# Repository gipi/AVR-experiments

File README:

This repository will contain projects AVR related.

Each project is contained in a directory of its own and in order to
compile it you can

 $ cd <project name>
 $ make upload

It's possible to install the dependencies using the
following command in a Debian-like sistem

 # apt-get install gcc-avr binutils-avr avr-libc

In the libraries/ directory are contained some routines very useful
to AVR projects. Are intended to be incluede in your source code
and not linked since it's very likely that the F_CPU or MCU values are
different from what you expect at compile time.

It's also possible to flash into Arduino this code (not all code will work)
using the ``PROGRAMMER`` variable:

    $ make PROGRAMMER=arduino

if not indicated will use the ``buspirate``. Obvioulsy the code must set the ``MCU``
and ``F_CPU`` accordingly.

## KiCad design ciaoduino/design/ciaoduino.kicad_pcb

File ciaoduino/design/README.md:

Design files created with kicad.

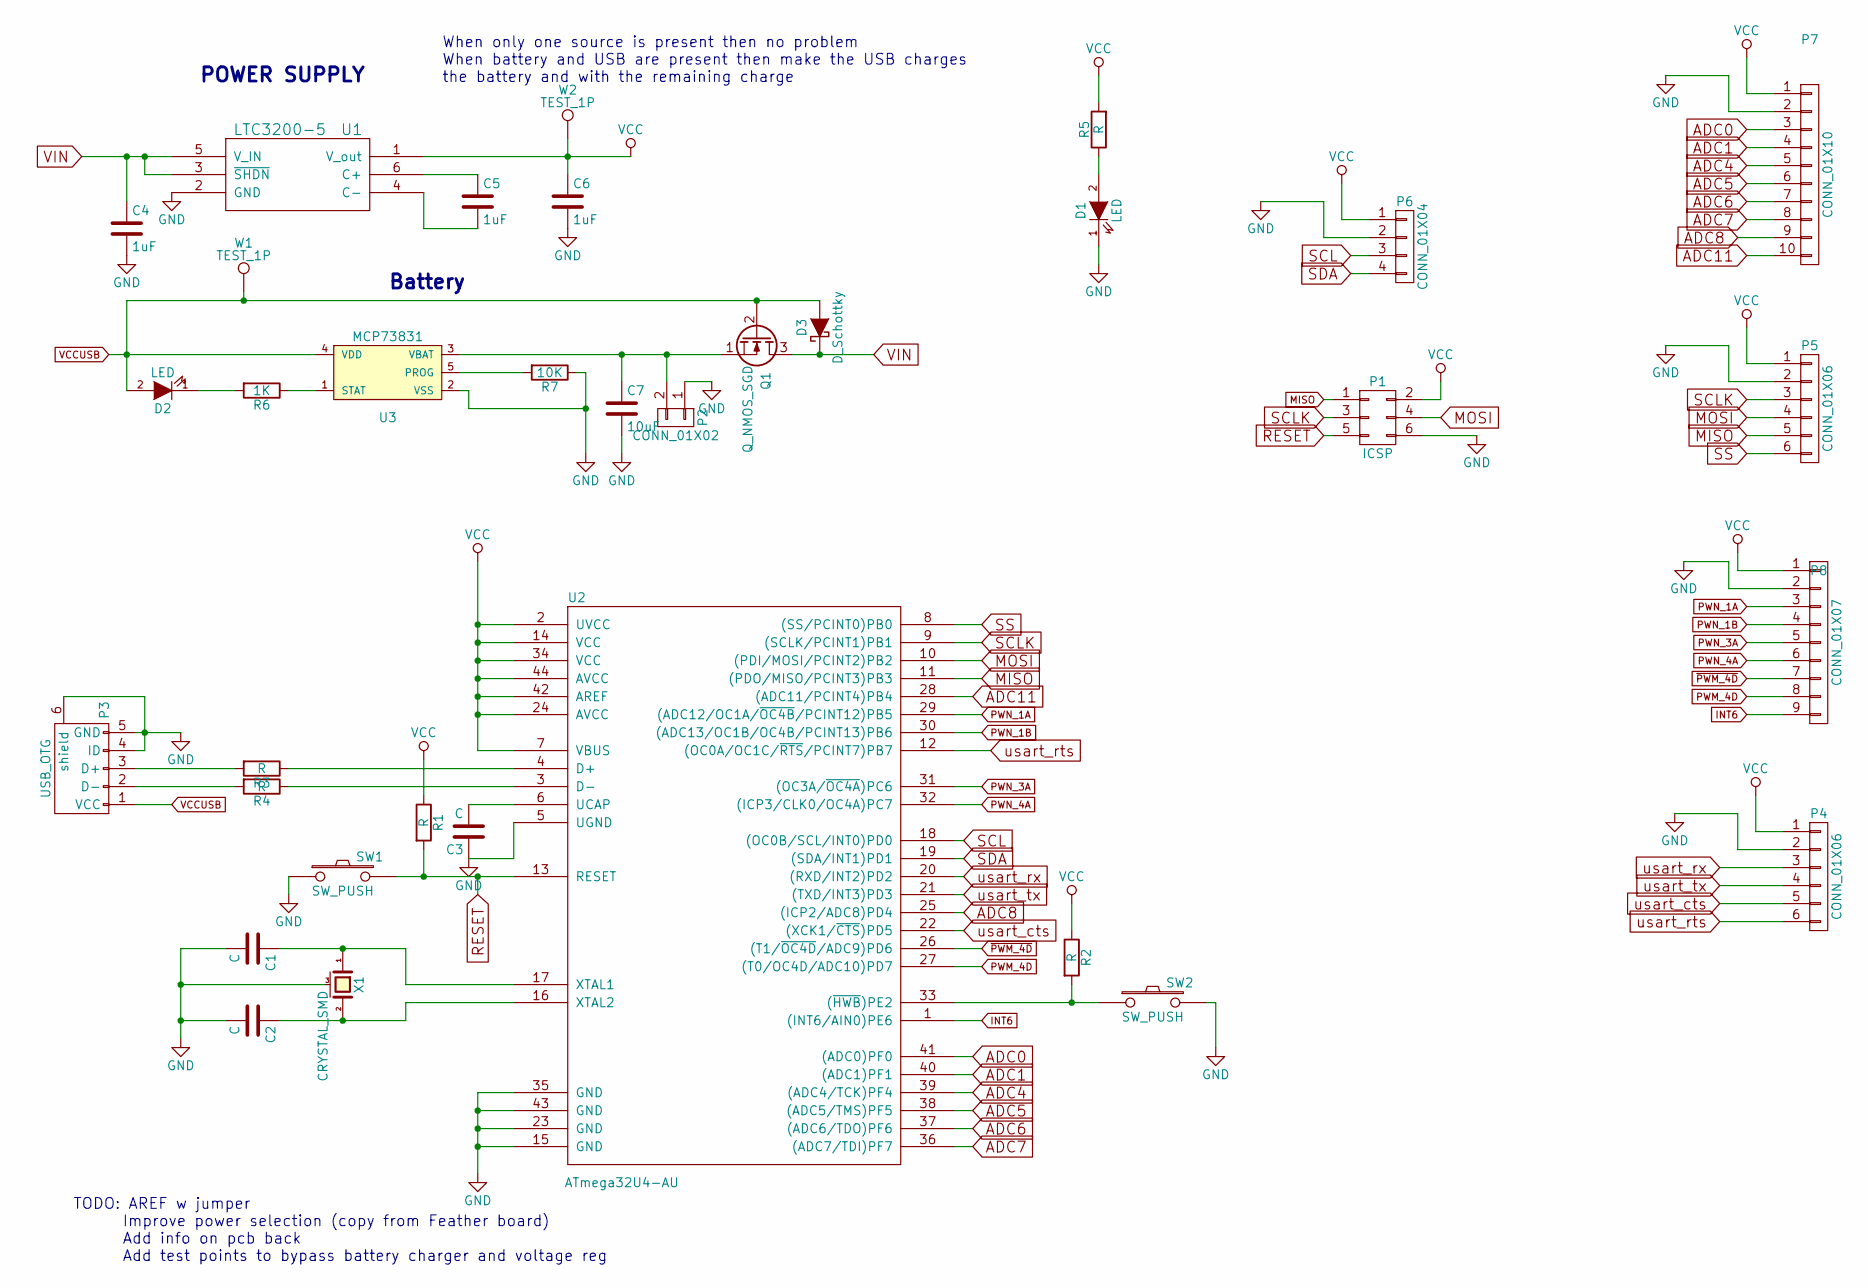
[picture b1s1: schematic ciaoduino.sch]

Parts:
C1, C2, C3: C; C_0603_HandSoldering
C4, C5, C6: 1uF; C_0603_HandSoldering
C7: 10uF; C_0603_HandSoldering
D1, D2: LED; LED_0603
D3: D_Schottky; DO-214AB
P1: ICSP; ICSP_SMD
P2: CONN_01X02; Pin_Header_Angled_1x02
P3: USB_OTG; USB_Mini-B
P4, P5: CONN_01X06; Pin_Header_Straight_1x06
P6: CONN_01X04; Pin_Header_Straight_1x04
P7: CONN_01X10; Pin_Header_Straight_1x10
P8: CONN_01X07; Pin_Header_Straight_1x09
Q1: Q_NMOS_SGD; SOT-23
R1, R3, R4, R5: R; R_0603
R2: R; R_0603_HandSoldering
R6: 1K; R_0603_HandSoldering
R7: 10K; R_0603_HandSoldering
SW1, SW2: SW_PUSH; SW_SPST_KMR2
U1: LTC3200-5; SOT-23-6_Handsoldering
U2: ATmega32U4-AU; TQFP-44_10x10mm_Pitch0.8mm
U3: MCP73831; SOT-23-5
W1, W2: TEST_1P; 1Pin
X1: CRYSTAL_SMD; crystal_FA238-TSX3225

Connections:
ADC0: P7.3, U2.41 ((ADC0)PF0)
ADC1: P7.4, U2.40 ((ADC1)PF1)
ADC4: P7.5, U2.39 ((ADC4/TCK)PF4)
ADC5: P7.6, U2.38 ((ADC5/TMS)PF5)
ADC6: P7.7, U2.37 ((ADC6/TDO)PF6)
ADC7: P7.8, U2.36 ((ADC7/TDI)PF7)
ADC8: P7.9, U2.25 ((ICP2/ADC8)PD4)
ADC11: P7.10, U2.28 ((ADC11/PCINT4)PB4)
GND: C1.2, C2.2, C3.1, C4.2, C6.2, C7.2, D1.1 (K), P1.6, P2.1, P3.4 (ID), P3.5 (GND), P3.6 (shield), P4.2, P5.2, P6.2, P7.2, P8.2, R7.1, SW1.1, SW2.2, U1.2 (GND), U2.5 (UGND), U2.15 (GND), U2.23 (GND), U2.35 (GND), U2.43 (GND), U3.2 (VSS), X1.3 (case)
INT6: P8.9, U2.1 ((INT6/AIN0)PE6)
MISO: P1.1, P5.5, U2.11 ((PDO/MISO/PCINT3)PB3)
MOSI: P1.4, P5.4, U2.10 ((PDI/MOSI/PCINT2)PB2)
unnamed: C1.1, U2.17 (XTAL1), X1.1
unnamed: C2.1, U2.16 (XTAL2), X1.2
unnamed: C3.2, U2.6 (UCAP)
unnamed: C5.1, U1.6 (C+)
unnamed: C5.2, U1.4 (C-)
unnamed: C7.1, P2.2, Q1.1 (S), U3.3 (VBAT)
unnamed: D1.2 (A), R5.1
unnamed: D2.1 (K), R6.2
unnamed: P3.2 (D-), R4.2
unnamed: P3.3 (D+), R3.2
unnamed: R2.2, SW2.1, U2.33 ((~HWB~)PE2)
unnamed: R3.1, U2.4 (D+)
unnamed: R4.1, U2.3 (D-)
unnamed: R6.1, U3.1 (STAT)
unnamed: R7.2, U3.5 (PROG)
PWM_4D: P8.8, U2.27 ((T0/OC4D/ADC10)PD7)
PWN_1A: P8.3, U2.29 ((ADC12/OC1A/~OC4B~/PCINT12)PB5)
PWN_1B: P8.4, U2.30 ((ADC13/OC1B/OC4B/PCINT13)PB6)
PWN_3A: P8.5, U2.31 ((OC3A/~OC4A~)PC6)
PWN_4A: P8.6, U2.32 ((ICP3/CLK0/OC4A)PC7)
RESET: P1.5, R1.2, SW1.2, U2.13 (RESET)
SCL: P6.3, U2.18 ((OC0B/SCL/INT0)PD0)
SCLK: P1.3, P5.3, U2.9 ((SCLK/PCINT1)PB1)
SDA: P6.4, U2.19 ((SDA/INT1)PD1)
SS: P5.6, U2.8 ((SS/PCINT0)PB0)
VCC: C6.1, P1.2, P4.1, P5.1, P6.1, P7.1, P8.1, R1.1, R2.1, R5.2, U1.1 (V_out), U2.2 (UVCC), U2.7 (VBUS), U2.14 (VCC), U2.24 (AVCC), U2.34 (VCC), U2.42 (AREF), U2.44 (AVCC), W2.1
VCCUSB: D2.2 (A), D3.2 (A), P3.1 (VCC), Q1.2 (G), U3.4 (VDD), W1.1
VIN: C4.1, D3.1 (K), Q1.3 (D), U1.3 (~SHDN), U1.5 (V_IN)
usart_cts: P4.5, U2.22 ((XCK1/~CTS~)PD5)
usart_rts: P4.6, U2.12 ((OC0A/OC1C/~RTS~/PCINT7)PB7)
usart_rx: P4.3, U2.20 ((RXD/INT2)PD2)
usart_tx: P4.4, U2.21 ((TXD/INT3)PD3)
~PWM_4D: P8.7, U2.26 ((T1/~OC4D~/ADC9)PD6)

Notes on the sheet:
TODO: AREF w jumper Improve power selection (copy from Feather board) Add info on pcb back Add test points to bypass battery charger and voltage reg
POWER SUPPLY
Battery
When only one source is present then no problem When battery and USB are present then make the USB charges the battery and with the remaining charge

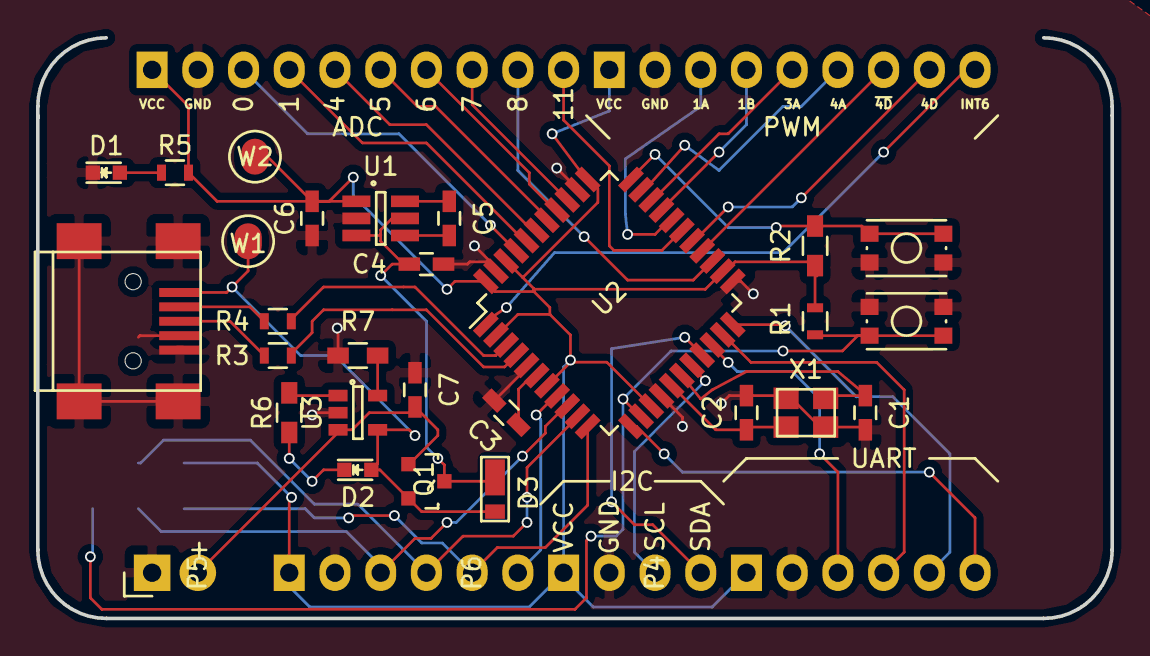
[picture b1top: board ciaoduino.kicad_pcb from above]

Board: 2 copper layers, 59.7 x 32.3 mm, 34 parts (1 on the bottom side), 45 nets.

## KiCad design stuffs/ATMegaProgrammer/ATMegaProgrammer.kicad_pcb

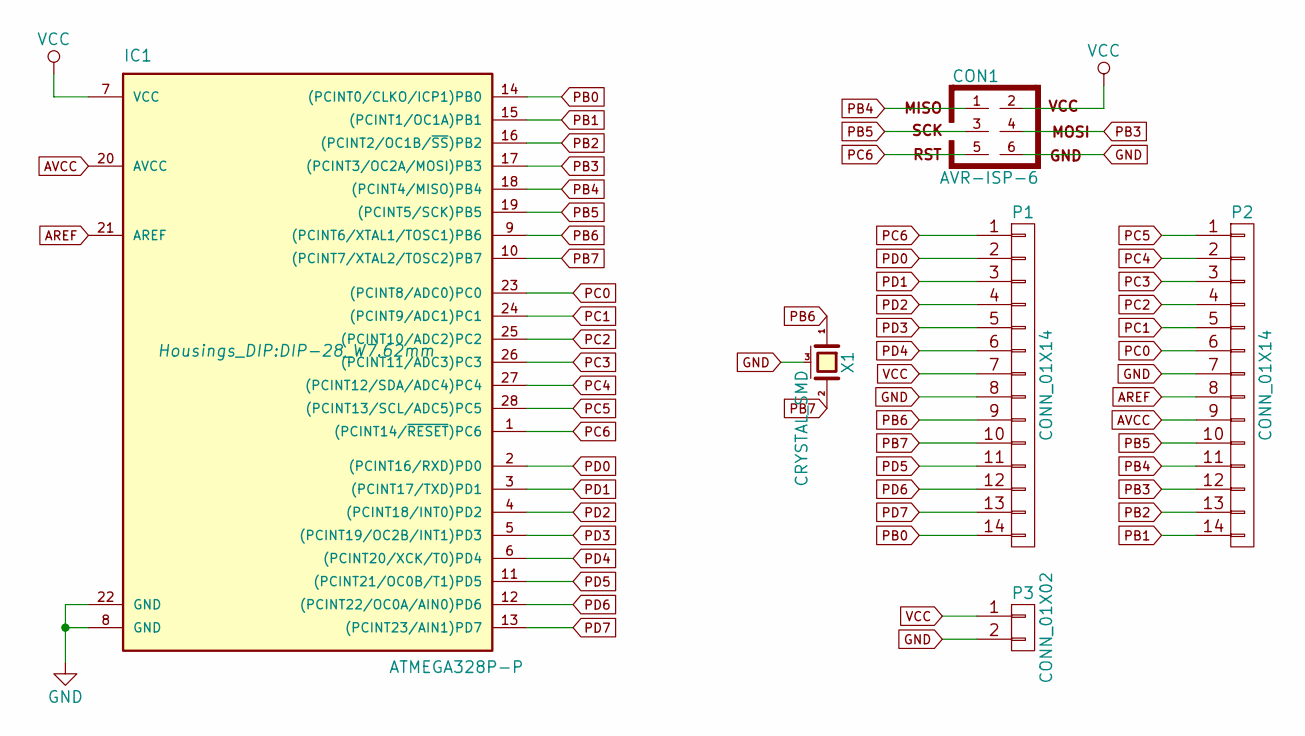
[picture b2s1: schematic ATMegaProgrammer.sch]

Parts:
CON1: AVR-ISP-6; Pin_Header_Straight_2x03
IC1: ATMEGA328P-P; DIP-28_W7.62mm
P1, P2: CONN_01X14; Pin_Header_Straight_1x14
P3: CONN_01X02; Pin_Header_Straight_1x02
X1: CRYSTAL_SMD; crystal_FA238-TSX3225

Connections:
AREF: IC1.21 (AREF), P2.8
AVCC: IC1.20 (AVCC), P2.9
GND: CON1.6, IC1.8 (GND), IC1.22 (GND), P1.8, P2.7, P3.2, X1.3 (case)
PB0: IC1.14 ((PCINT0/CLKO/ICP1)PB0), P1.14
PB1: IC1.15 ((PCINT1/OC1A)PB1), P2.14
PB2: IC1.16 ((PCINT2/OC1B/~SS~)PB2), P2.13
PB3: CON1.4, IC1.17 ((PCINT3/OC2A/MOSI)PB3), P2.12
PB4: CON1.1, IC1.18 ((PCINT4/MISO)PB4), P2.11
PB5: CON1.3, IC1.19 ((PCINT5/SCK)PB5), P2.10
PB6: IC1.9 ((PCINT6/XTAL1/TOSC1)PB6), P1.9, X1.1
PB7: IC1.10 ((PCINT7/XTAL2/TOSC2)PB7), P1.10, X1.2
PC0: IC1.23 ((PCINT8/ADC0)PC0), P2.6
PC1: IC1.24 ((PCINT9/ADC1)PC1), P2.5
PC2: IC1.25 ((PCINT10/ADC2)PC2), P2.4
PC3: IC1.26 ((PCINT11/ADC3)PC3), P2.3
PC4: IC1.27 ((PCINT12/SDA/ADC4)PC4), P2.2
PC5: IC1.28 ((PCINT13/SCL/ADC5)PC5), P2.1
PC6: CON1.5, IC1.1 ((PCINT14/~RESET~)PC6), P1.1
PD0: IC1.2 ((PCINT16/RXD)PD0), P1.2
PD1: IC1.3 ((PCINT17/TXD)PD1), P1.3
PD2: IC1.4 ((PCINT18/INT0)PD2), P1.4
PD3: IC1.5 ((PCINT19/OC2B/INT1)PD3), P1.5
PD4: IC1.6 ((PCINT20/XCK/T0)PD4), P1.6
PD5: IC1.11 ((PCINT21/OC0B/T1)PD5), P1.11
PD6: IC1.12 ((PCINT22/OC0A/AIN0)PD6), P1.12
PD7: IC1.13 ((PCINT23/AIN1)PD7), P1.13
VCC: CON1.2, IC1.7 (VCC), P1.7, P3.1

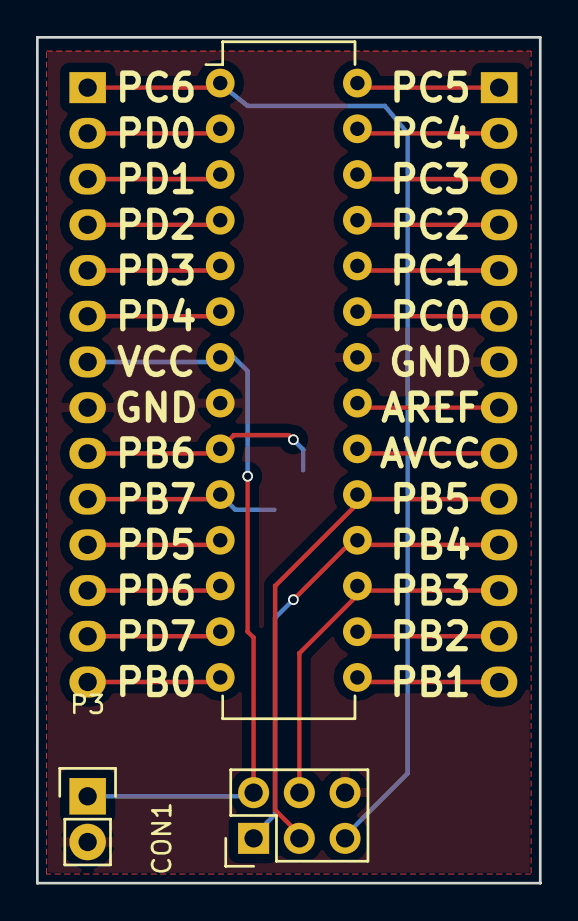
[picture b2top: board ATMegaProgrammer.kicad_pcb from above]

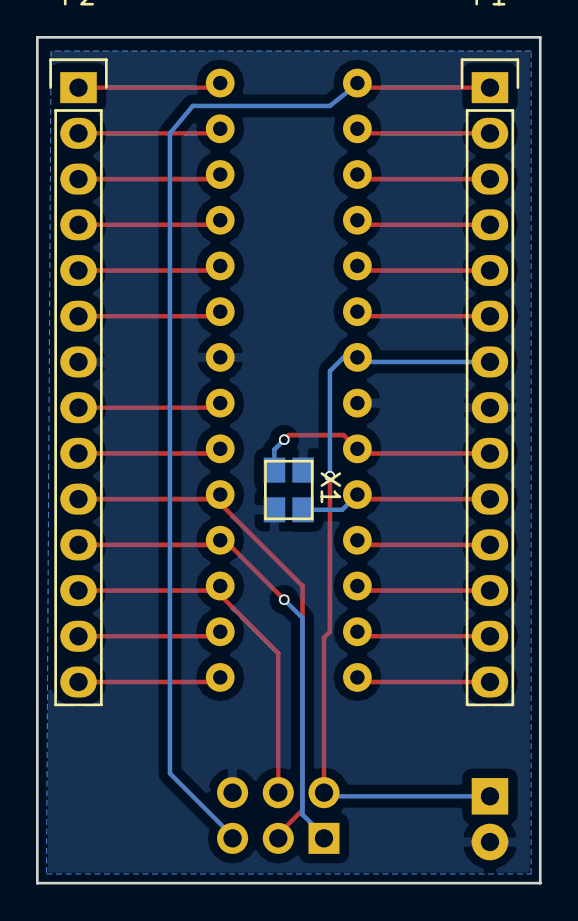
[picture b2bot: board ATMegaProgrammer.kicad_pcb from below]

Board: 2 copper layers, 27.9 x 47.0 mm, 6 parts (3 on the bottom side), 27 nets.

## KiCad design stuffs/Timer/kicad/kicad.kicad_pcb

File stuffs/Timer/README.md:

# TM1637

This is a chip designed to drive a seven segment display

## Links

 - [Library source code](https://github.com/avishorp/TM1637)
 - [Groove 4-digit display](http://www.seeedstudio.com/wiki/Grove_-_4-Digit_Display)

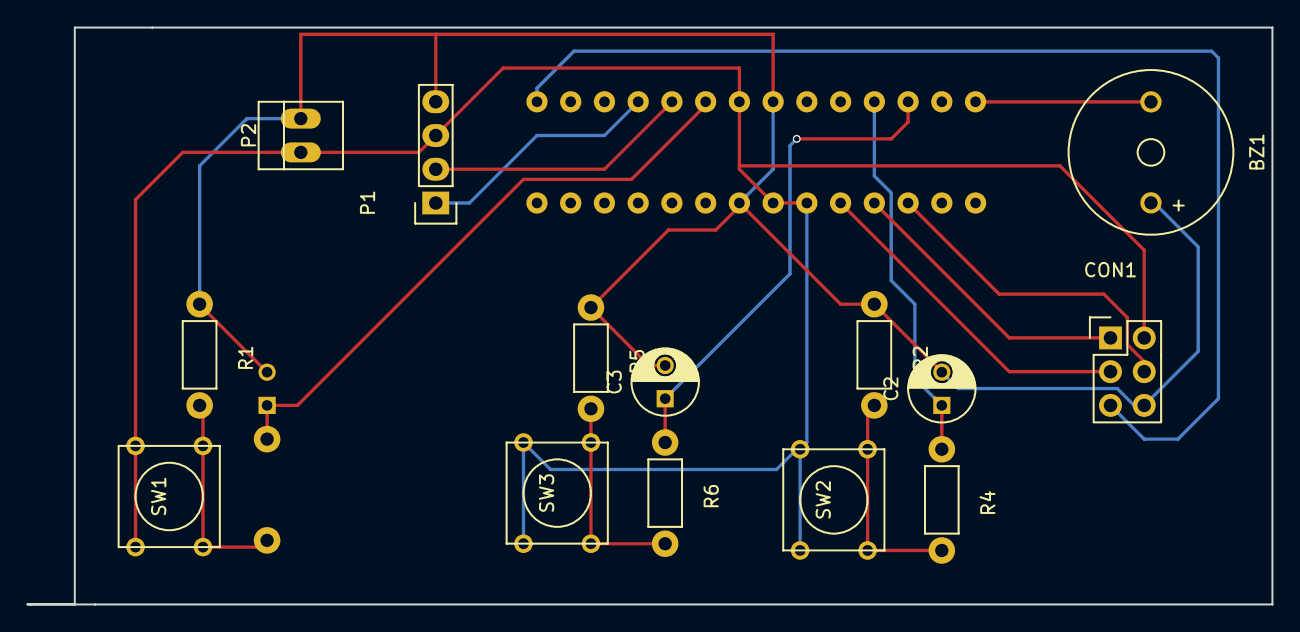
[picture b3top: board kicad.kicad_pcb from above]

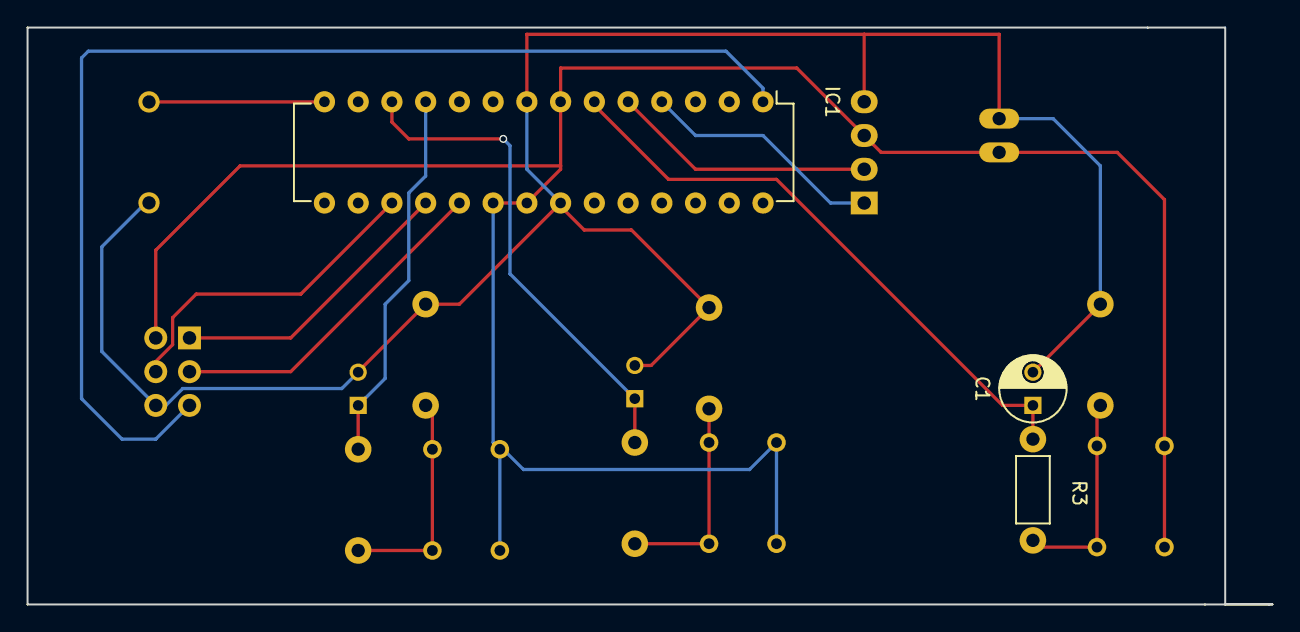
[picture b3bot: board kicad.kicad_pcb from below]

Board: 2 copper layers, 93.7 x 43.4 mm, 17 parts (3 on the bottom side), 15 nets.

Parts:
BZ1: buzzer; MagneticBuzzer_ProSignal_ABI-009-RC
C1, C2, C3: 10uF; C_Radial_D5_L6_P2.5
CON1: AVR-ISP-6; Pin_Header_Straight_2x03
IC1: ATMEGA328P-P; DIP-28_W7.62mm
P1: CONN_01X04; Socket_Strip_Straight_1x04
P2: CONN_01X02; PINHEAD1-2
R1, R2, R5: 10; Resistor_Horizontal_RM7mm
R3, R4, R6: 1K; Resistor_Horizontal_RM7mm
SW1, SW2, SW3: SW_PUSH; SW_PUSH_SMALL

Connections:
DECREASE: C3.1, IC1.12, R6.1
DISPLAY_CLK: IC1.4, P1.1
DISPLAY_IO: IC1.5, P1.2
GND: BZ1.2, C1.2, C2.2, C3.2, CON1.6, IC1.8, IC1.22, P1.4, P2.2, R1.1, R2.1, R5.1
INCREASE: C2.1, IC1.11, R4.1
unnamed: BZ1.1, IC1.14
unnamed: CON1.1, IC1.18
unnamed: CON1.3, IC1.19
unnamed: CON1.4, IC1.17
unnamed: CON1.5, IC1.1
unnamed: R1.2, R3.2, SW1.2
unnamed: R2.2, R4.2, SW2.2
unnamed: R5.2, R6.2, SW3.2
PLAY: C1.1, IC1.6, R3.1
VCC: CON1.2, IC1.7, IC1.20, IC1.21, P1.3, P2.1, SW1.1, SW2.1, SW3.1

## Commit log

2012-11-21 Initial import.
2012-11-23 Add some info and the Arduino Makefile.
2012-11-23 Ignore build directory.
2012-11-23 Move file.
2012-11-26 First attempt to use USART with ATMega328.
2012-11-26 Create an echo application with USART.
2012-11-26 Fix F_CPU.
2012-11-26 Make blink the led on pin 13 of a standard Arduino.
2012-11-26 Add Makefile that not uses Arduino build system.
2012-11-26 Ignore hex and object files.
2012-12-01 Add UART software implementation for attiny85.
2012-12-01 Use CC.
2012-12-01 make the compiler output warnings.
2012-12-01 Remove also the target.
2012-12-02 Remove useless #defines.
2012-12-02 Fix digitalRead().
    (PINB & (1 << n)) doesn't return 1 but a number != 0.
2012-12-02 Fix return value.
2012-12-02 Fix serial_read().
2012-12-02 Make an echo UART example program.
2012-12-04 Remove useless definition.
2012-12-04 Make less verbose avrdude output.
2012-12-04 Reorganize Makefile.
    Create a Makefile for each project which must define TARGET and OBJ_FILES
    variable in order to indicate to the build system what to build.
2012-12-04 Update README.
2012-12-04 Add rules to manage EEPROM images.
2012-12-04 Fix upload rules.
2012-12-04 Fix files to ignore.
2012-12-04 Refactor makefiles.
    There are two sub makefiles, one with the default value of various
    variables and one with the predefined targets. In the projects' Makefile
    we must define at least OBJ_FILES and TARGET variables.
2012-12-04 Add target showing size occupation in a ELF avr file.
2012-12-04 Add blinky's Makefile.
2012-12-04 First attempt to understand memory in AVR.
2012-12-04 Use TARGETS for the default target.
2012-12-04 Make the warning be errors.
    So we can be alerted on trivial mistakes.
2012-12-04 Use pin 0.
2012-12-09 Move code in a directory of its own.
2012-12-09 Factorize code aout UART software implementation.
2012-12-09 Add Makefile for at85_serial.
2012-12-09 Fix Makefile in order to be able to compile with "libraries".
2012-12-16 Add shift register code.
2012-12-16 Add some #ifdef conditions.
2012-12-16 Factorize code about pins macro.
2012-12-16 Complete example with shift register.
2012-12-16 Add missing F_CPU value.
2012-12-16 Fix missing include.
2012-12-16 More info.
2012-12-18 uart: add serial_init().
2012-12-18 Fix typo.
2015-05-21 Make possible to upload code to Arduino.
2015-05-21 First working code for ADC.
2015-05-28 Add example for SPI communication.
2015-05-29 More complete SPI example with attiny85 a display and a button.
2015-07-20 Add dump target.
2015-07-20 Change variable assigment.
2015-07-20 Add usb type programmer.
2015-10-15 Add rules to build using the Arduino's libraries.
2015-10-15 Fix wording.
2015-10-16 Rework Makefile related to ciaoduino.
2015-10-16 Prettify arduino related document.
2015-10-16 Add example of the USART communication using the Serial1 object.
    This mimics the Leonardo board.
2015-10-16 Explain what ciaoduino is.
2015-10-16 Put blink example in a dir of its own.
2015-10-18 Add arduino code for ADXL345 sensor.
2015-10-18 More pragmatic output.
2015-10-30 Add note to need for cpp type of file for Arduino.
2015-11-18 Add code associated with GY9255.
2015-11-18 Renaming to avoid chinese characters.
2015-11-18 Update code from original repo.
    https://github.com/Snowda/MPU9250
2015-11-18 Add note about delay() using Timer0.
2015-11-24 Add code for i2c_scanner.
    Taken from here <http://playground.arduino.cc/Main/I2cScanner>.
2016-03-28 Add keyboard code for ciaoduino stolen from Arduino Leonardo example.
2016-03-29 First design file created using kicad for ciaoduino.
2016-03-29 Move sketches into directory firmwares.
2016-04-09 Make more realistic board.
2016-04-11 Add protocol connectors.
2016-04-12 Route ADC related IO pins.
2016-04-26 Add section about TM1637.
2016-04-27 Start a project to create a timer.
2016-04-27 Add function generator.
2016-04-28 Add a start/pause button.
2016-04-29 add missing variable.
2016-05-21 Update and refactor code and schematics for timer.
2016-05-21 First implementation of alarm.
2016-05-22 Update Timer kicad project.
2016-05-22 Update kicad files for Timer project.
2016-05-23 Update kicad design files.
2016-07-05 Add simple project of ATMega328P programmer.
    It includes an ISPC header per simple programming and exposes all the
    microcontroller pins.
2016-07-05 Improve ATMega328Programmer.
2016-07-06 Add ground planes, fix labels and connect GND for crystal.
2016-07-06 First release of the board.
2016-07-10 Update ciaoduino design.
2016-07-13 Rework layout.
2016-07-14 Update board with UCAP pad connected.
2016-07-14 Add mounting hole and reworked edges.
2016-07-14 Rework I2C header footprint.
2016-07-18 ciaoduino: rework board.
2016-08-05 Timer: create SMD layout.
2016-08-05 Set clock prescaler.
2016-08-05 Update timer immediately.
2016-08-06 Add also the decrease button handling.
2016-08-06 Use showTimer().
2016-08-06 Make the display blink when an action is performed.
2016-08-06 Factorize values with some #defines.
2016-08-06 Fix counter for a 8MHz clock.
2016-12-30 Reorganize pinout.
2016-12-30 ciaoduino: add OSHW logo with copper and soldermask.
2017-01-02 ciaoduino: add some info.
2017-01-03 ciaoduino: complete a messy routing.
2017-02-19 timer: add a WIP of a case designed with freecad.
2017-02-19 timer: add button outline in the base sketch.
2017-02-19 timer: add sketch for display outline.
2017-02-20 timer: almost completed case.
